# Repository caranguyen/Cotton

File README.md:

# Cotton
Contains project files for USDA-ARS research projects

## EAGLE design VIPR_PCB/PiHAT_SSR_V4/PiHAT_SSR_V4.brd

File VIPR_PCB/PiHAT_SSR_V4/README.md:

# 4th rev of the VIPR Raspberry Pi solid state relay board
- Removed two solid-state relays to allow for high side switching and flyback diodes on solenoids
- Needing to reorient components on board to allow for better isolation of 12V solenoid power and ground from Raspberry Pi

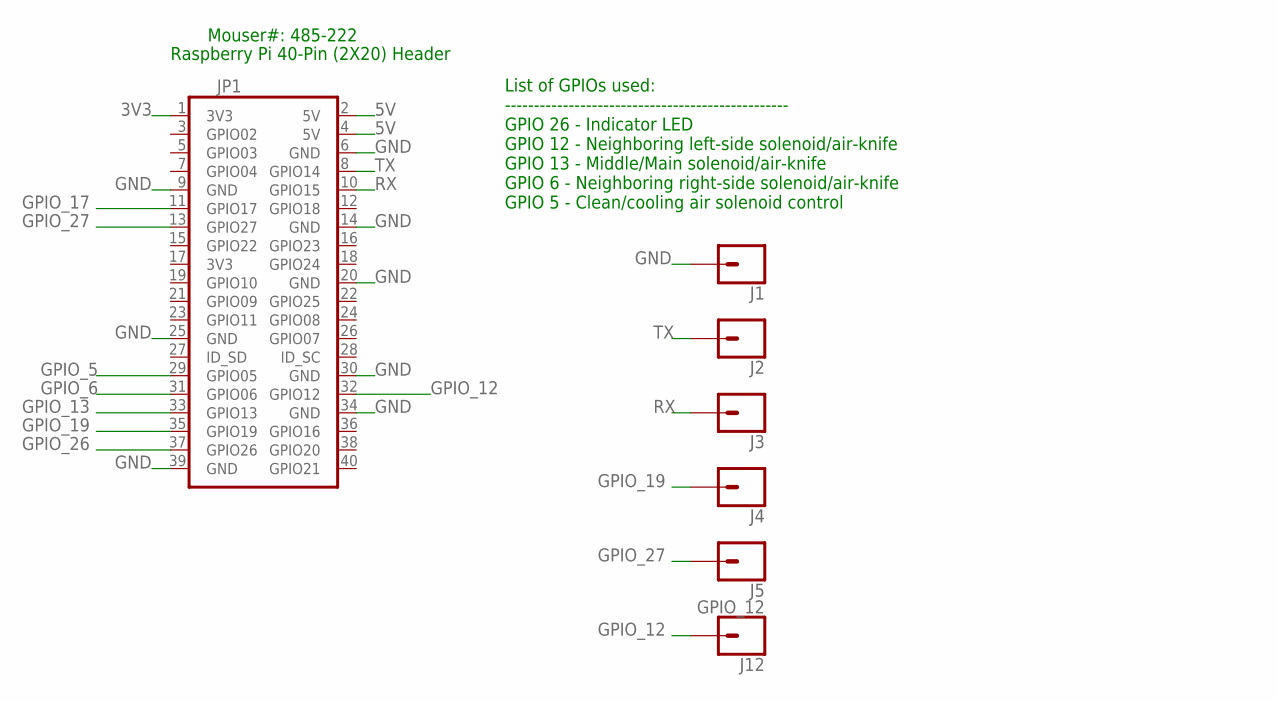
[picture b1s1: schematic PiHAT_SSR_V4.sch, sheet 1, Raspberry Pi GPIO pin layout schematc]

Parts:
J1, J2, J3, J4, J5: CONN_01; 1X01
J12: GPIO_12; 1X01
JP1: 40W_PI_HAT_TPH; 2X20

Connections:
3V3: JP1.1 (3V3); also elsewhere on the board
5V: JP1.2 (5V), JP1.4 (5V); also elsewhere on the board
GND: J1.1, JP1.6 (GND), JP1.9 (GND), JP1.14 (GND), JP1.20 (GND), JP1.25 (GND), JP1.30 (GND), JP1.34 (GND), JP1.39 (GND); also elsewhere on the board
GPIO_5: JP1.29 (GPIO05); also elsewhere on the board
GPIO_6: JP1.31 (GPIO06); also elsewhere on the board
GPIO_12: J12.1, JP1.32 (GPIO12)
GPIO_13: JP1.33 (GPIO13); also elsewhere on the board
GPIO_17: JP1.11 (GPIO17); also elsewhere on the board
GPIO_19: J4.1, JP1.35 (GPIO19)
GPIO_26: JP1.37 (GPIO26)
GPIO_27: J5.1, JP1.13 (GPIO27)
RX: J3.1, JP1.10 (GPIO15)
TX: J2.1, JP1.8 (GPIO14)

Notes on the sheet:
Raspberry Pi 40-Pin (2X20) Header
List of GPIOs used: ------------------------------------------------- GPIO 26 - Indicator LED GPIO 12 - Neighboring left-side solenoid/air-knife GPIO 13 - Middle/Main solenoid/air-knife GPIO 6 - Neighboring right-side solenoid/air-knife GPIO 5 - Clean/cooling air solenoid control
Mouser#: 485-222

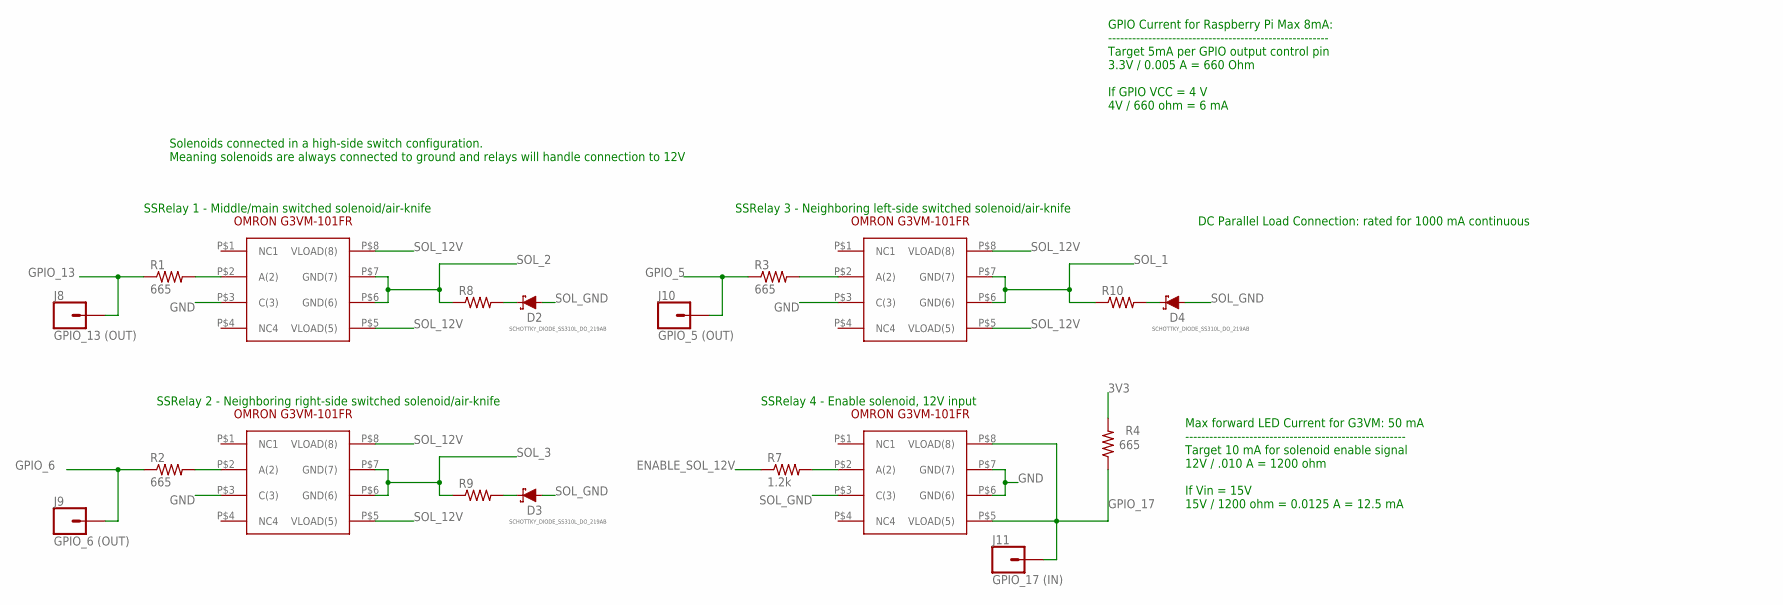
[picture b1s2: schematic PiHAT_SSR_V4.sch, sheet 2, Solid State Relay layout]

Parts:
D2, D3, D4: SCHOTTKY_DIODE_SS310L_DO_219AB; SCHOTTKY_DIODE_DO219AB
J8: GPIO_13 (OUT); 1X01
J9: GPIO_6 (OUT); 1X01
J10: GPIO_5 (OUT); 1X01
J11: GPIO_17 (IN); 1X01
R1, R2, R3, R4: 665; M0805
R7: 1.2k; M0805
R8, R9, R10: R-US_R2512; R2512
SSR1, SSR2, SSR3, SSR4: OMRON_G3VM_101FR; OMRON_G3VM-101FR

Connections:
3V3: R4.2; also elsewhere on the board
ENABLE_SOL_12V: R7.1; also elsewhere on the board
GND: SSR1.P$3 (C(3)), SSR2.P$3 (C(3)), SSR3.P$3 (C(3)), SSR4.P$6 (GND(6)), SSR4.P$7 (GND(7)); also elsewhere on the board
GPIO_5: J10.1, R3.1; also elsewhere on the board
GPIO_6: J9.1, R2.1; also elsewhere on the board
GPIO_13: J8.1, R1.1; also elsewhere on the board
GPIO_17: J11.1, R4.1, SSR4.P$5 (VLOAD(5)), SSR4.P$8 (VLOAD(8)); also elsewhere on the board
unnamed: D2.P$2 (C), R8.2
unnamed: R3.2, SSR3.P$2 (A(2))
unnamed: D3.P$2 (C), R9.2
unnamed: R2.2, SSR2.P$2 (A(2))
unnamed: R1.2, SSR1.P$2 (A(2))
unnamed: R7.2, SSR4.P$2 (A(2))
unnamed: D4.P$2 (C), R10.2
SOL_1: R10.1, SSR3.P$6 (GND(6)), SSR3.P$7 (GND(7)); also elsewhere on the board
SOL_2: R8.1, SSR1.P$6 (GND(6)), SSR1.P$7 (GND(7)); also elsewhere on the board
SOL_3: R9.1, SSR2.P$6 (GND(6)), SSR2.P$7 (GND(7)); also elsewhere on the board
SOL_12V: SSR1.P$5 (VLOAD(5)), SSR1.P$8 (VLOAD(8)), SSR2.P$5 (VLOAD(5)), SSR2.P$8 (VLOAD(8)), SSR3.P$5 (VLOAD(5)), SSR3.P$8 (VLOAD(8)); also elsewhere on the board
SOL_GND: D2.P$1 (A), D3.P$1 (A), D4.P$1 (A), SSR4.P$3 (C(3)); also elsewhere on the board

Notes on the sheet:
SSRelay 2 - Neighboring right-side switched solenoid/air-knife
SSRelay 1 - Middle/main switched solenoid/air-knife
SSRelay 3 - Neighboring left-side switched solenoid/air-knife
SSRelay 4 - Enable solenoid, 12V input
GPIO Current for Raspberry Pi Max 8mA: ------------------------------------------------------- Target 5mA per GPIO output control pin 3.3V / 0.005 A = 660 Ohm If GPIO VCC = 4 V 4V / 660 ohm = 6 mA
Max forward LED Current for G3VM: 50 mA ------------------------------------------------------- Target 10 mA for solenoid enable signal 12V / .010 A = 1200 ohm If Vin = 15V 15V / 1200 ohm = 0.0125 A = 12.5 mA
DC Parallel Load Connection: rated for 1000 mA continuous
Solenoids connected in a high-side switch configuration. Meaning solenoids are always connected to ground and relays will handle connection to 12V

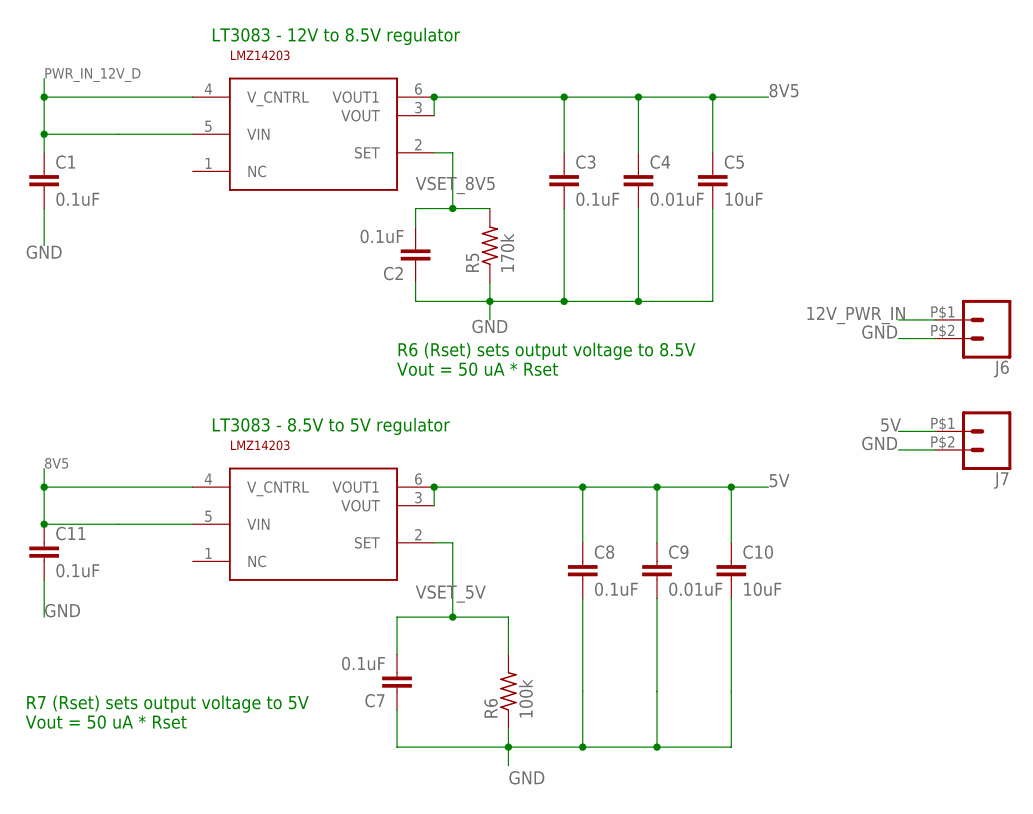
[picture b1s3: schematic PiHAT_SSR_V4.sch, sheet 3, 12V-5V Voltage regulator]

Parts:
C1, C2, C3, C7, C8, C11: 0.1uF; C0805
C4, C9: 0.01uF; C0805
C5, C10: 10uF; C0805
J6, J7: CONN_02PTH2; 1X02_BIG
R5: 170k; M0805
R6: 100k; M0805
VR1, VR2: SMD-SPECIAL_28PIN_PIC32_11_3_2011_LT3083; SMD-SPECIAL_28PIN_PIC32_11_3_2011_DPAK-5

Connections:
5V: C8.1, C9.1, C10.1, J7.P$1 (1), VR2.3 (VOUT), VR2.6 (VOUT1); also elsewhere on the board
8V5: C3.1, C4.1, C5.1, C11.1, VR1.3 (VOUT), VR1.6 (VOUT1), VR2.4 (V_CNTRL), VR2.5 (VIN)
12V_PWR_IN: J6.P$1 (1); also elsewhere on the board
GND: C1.2, C2.1, C3.2, C4.2, C5.2, C7.1, C8.2, C9.2, C10.2, C11.2, J6.P$2 (2), J7.P$2 (2), R5.1, R6.1; also elsewhere on the board
PWR_IN_12V_D: C1.1, VR1.4 (V_CNTRL), VR1.5 (VIN); also elsewhere on the board
VSET_5V: C7.2, R6.2, VR2.2 (SET)
VSET_8V5: C2.2, R5.2, VR1.2 (SET)

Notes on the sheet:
LT3083 - 12V to 8.5V regulator
R6 (Rset) sets output voltage to 8.5V Vout = 50 uA * Rset
LT3083 - 8.5V to 5V regulator
R7 (Rset) sets output voltage to 5V Vout = 50 uA * Rset

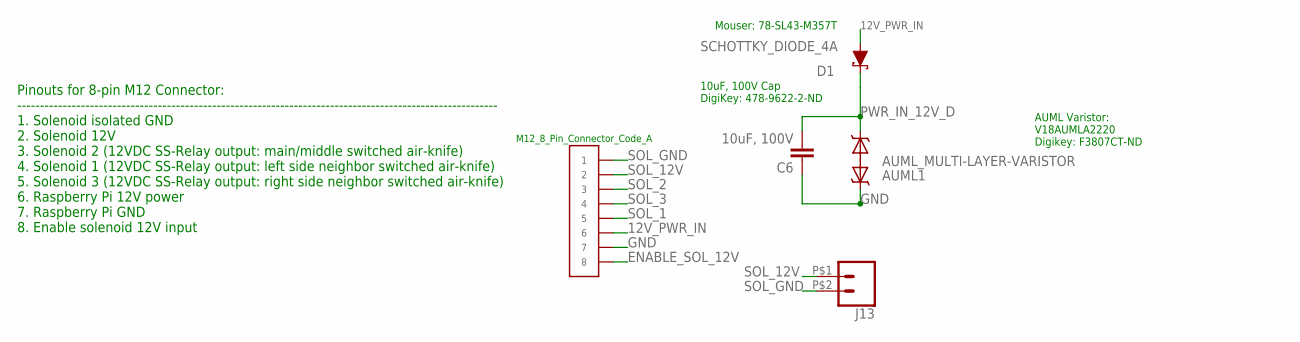
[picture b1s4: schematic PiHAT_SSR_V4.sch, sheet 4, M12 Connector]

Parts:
AUML1: SMD-SPECIAL_28PIN_PIC32_11_3_2011_MOD5_20_13_AUML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; SMD-SPECIAL_28PIN_PIC32_11_3_2011_MOD5_20_13_SMT_CAP_2220
C6: 10uF, 100V; C2220K
CN1: M12_8PIN_CODE_A
D1: SCHOTTKY_DIODE_4A; SCHOTTKY_DIODE_SMD_DO-214AB
J13: CONN_02PTH2; 1X02_BIG

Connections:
12V_PWR_IN: CN1.P$6, D1.P$2 (A); also elsewhere on the board
ENABLE_SOL_12V: CN1.P$8; also elsewhere on the board
GND: AUML1.1, C6.1, CN1.P$7; also elsewhere on the board
PWR_IN_12V_D: AUML1.2, C6.2, D1.P$1 (C); also elsewhere on the board
SOL_1: CN1.P$5; also elsewhere on the board
SOL_2: CN1.P$3; also elsewhere on the board
SOL_3: CN1.P$4; also elsewhere on the board
SOL_12V: CN1.P$2, J13.P$1 (1); also elsewhere on the board
SOL_GND: CN1.P$1, J13.P$2 (2); also elsewhere on the board

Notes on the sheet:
Pinouts for 8-pin M12 Connector: ---------------------------------------------------------------------------------------------------------- 1. Solenoid isolated GND 2. Solenoid 12V 3. Solenoid 2 (12VDC SS-Relay output: main/middle switched air-knife) 4. Solenoid 1 (12VDC SS-Relay output: left side 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
AUML_MULTI-LAYER-VARISTOR
10uF, 100V Cap DigiKey: 478-9622-2-ND
AUML Varistor: V18AUMLA2220 Digikey: F3807CT-ND
Mouser: 78-SL43-M357T

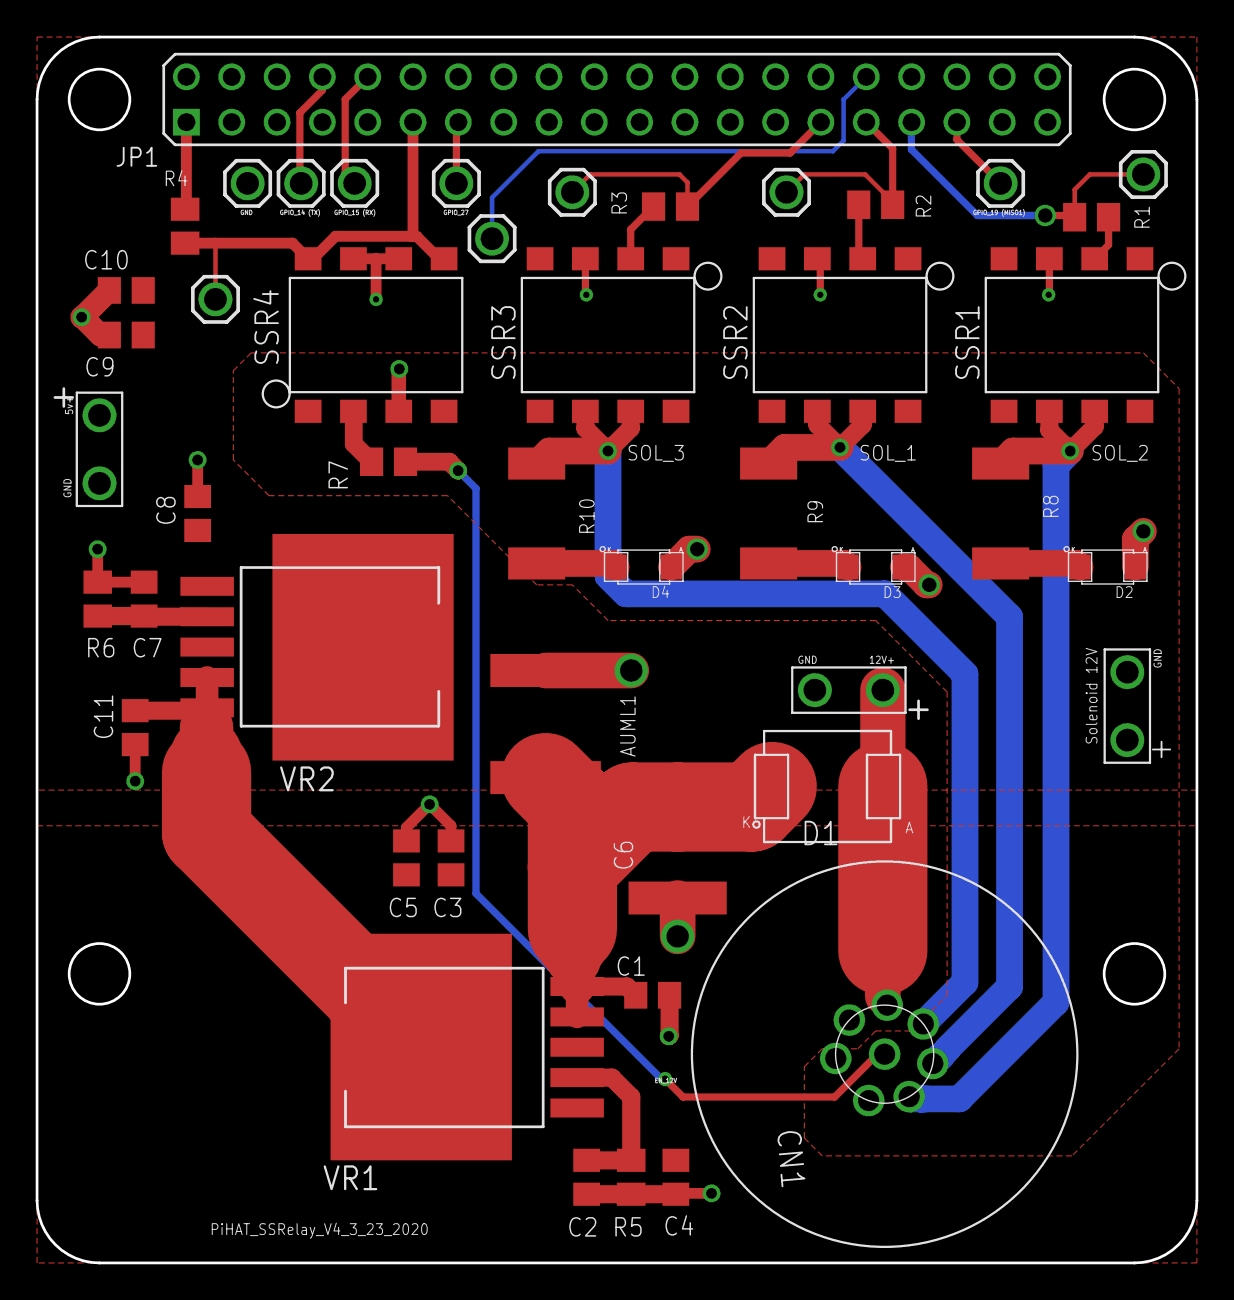
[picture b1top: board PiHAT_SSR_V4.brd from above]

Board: 2 copper layers, 65.0 x 68.7 mm, 47 parts (0 on the bottom side), 30 nets.

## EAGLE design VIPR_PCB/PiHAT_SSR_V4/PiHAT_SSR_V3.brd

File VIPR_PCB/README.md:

# VIPR PCB
Contains EAGLE files for the development of the Raspberry Pi solid-state relay board

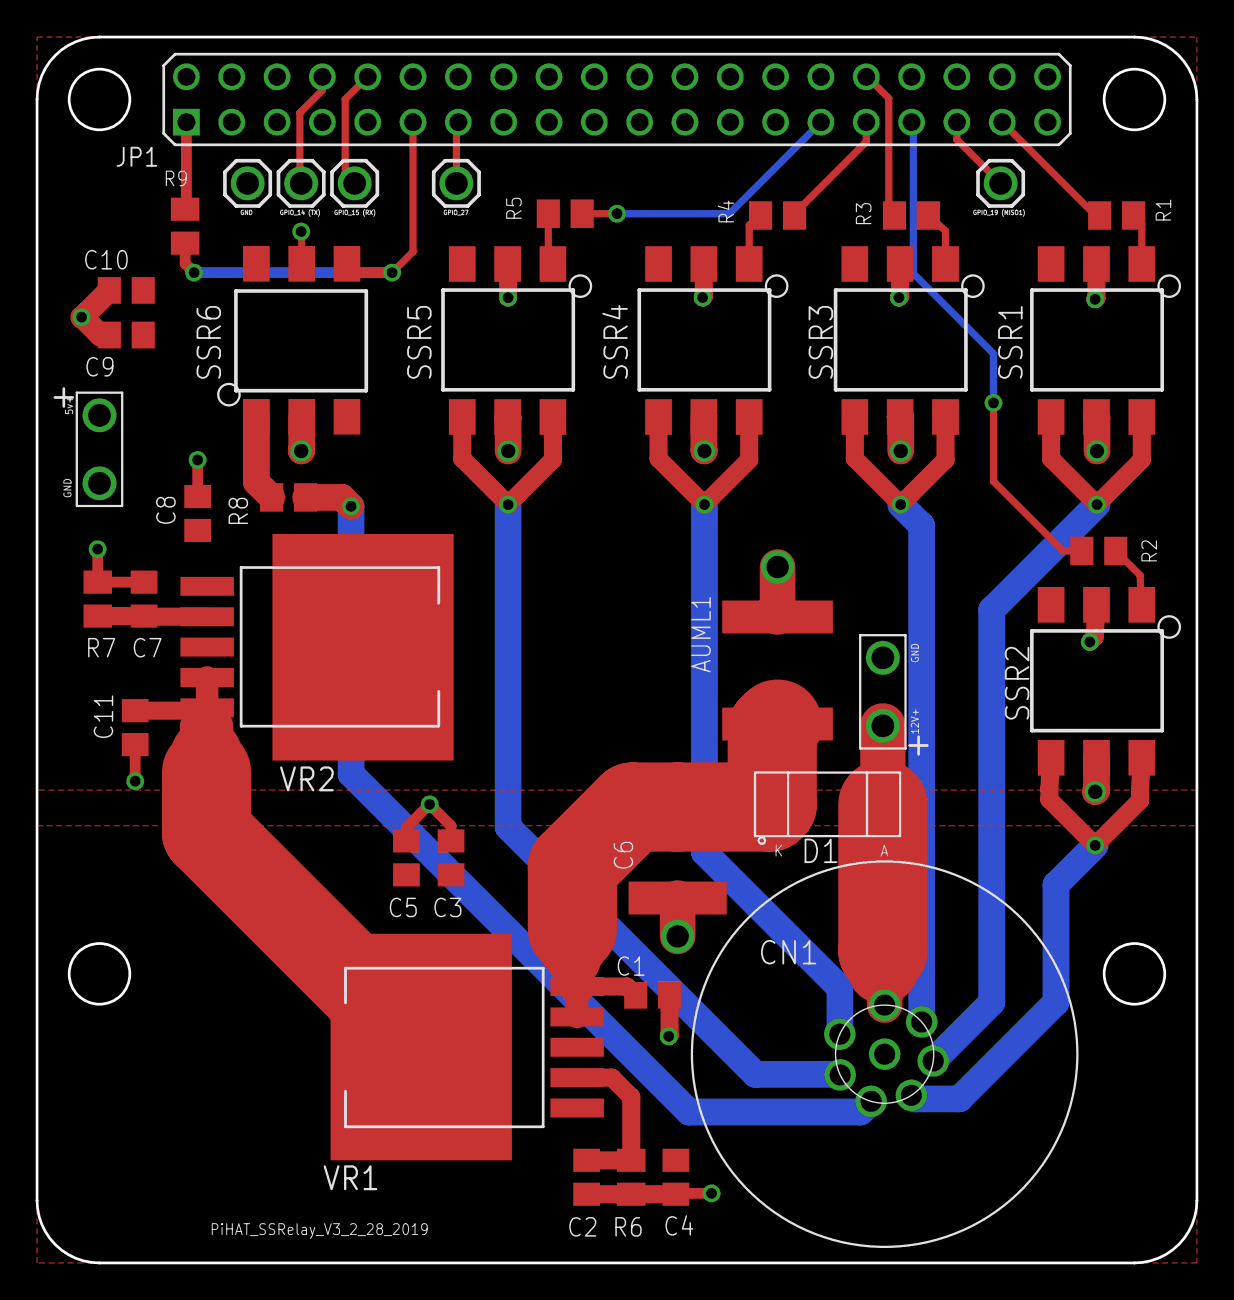
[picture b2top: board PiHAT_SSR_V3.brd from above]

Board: 2 copper layers, 65.0 x 68.7 mm, 39 parts (0 on the bottom side), 30 nets.

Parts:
AUML1: SMD-SPECIAL_28PIN_PIC32_11_3_2011_MOD5_20_13_AUML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; SMD-SPECIAL_28PIN_PIC32_11_3_2011_MOD5_20_13_SMT_CAP_2220
C1, C2, C3, C7, C8, C11: 0.1uF; C0805
C4, C9: 0.01uF; C0805
C5, C10: 10uF; C0805
C6: 10uF, 100V; C2220K
CN1: M12_8PIN_CODE_A
D1: SCHOTTKY_DIODE_4A; SCHOTTKY_DIODE_SMD_DO-214AB
J1, J2, J3, J4, J5: 1X01
J6, J7: 1X02_BIG
JP1: 2X20
R1, R2, R3, R4, R5, R9: 665; M0805
R6: 170k; M0805
R7: 100k; M0805
R8: 1.2k; M0805
SSR1, SSR2, SSR3, SSR4, SSR5, SSR6: SPARKFUN_OPTO_SSRELAY_OMRON_G3VM-61E1; SPARKFUN_6-SMD_OMRON_SSRELAY
VR1, VR2: SMD-SPECIAL_28PIN_PIC32_11_3_2011_LT3083; SMD-SPECIAL_28PIN_PIC32_11_3_2011_DPAK-5

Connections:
3V3: JP1.1, R9.2
5V: C8.1, C9.1, C10.1, J7.P$1, JP1.2, JP1.4, VR2.3, VR2.6
8V5: C3.1, C4.1, C5.1, C11.1, VR1.3, VR1.6, VR2.4, VR2.5
12V_PWR_IN: CN1.P$1, D1.P$2, J6.P$1
ENABLE_SOL_12V: CN1.P$4, R8.1
GND: AUML1.1, C1.2, C2.1, C3.2, C4.2, C5.2, C6.1, C7.1, C8.2, C9.2, C10.2, C11.2, CN1.P$8, J1.1, J6.P$2, J7.P$2, JP1.6, JP1.9, JP1.14, JP1.20, JP1.25, JP1.30, JP1.34, JP1.39, R6.1, R7.1, SSR1.2, SSR1.5, SSR2.2, SSR2.5, SSR3.2, SSR3.5, SSR4.2, SSR4.5, SSR5.2, SSR5.5, SSR6.2, SSR6.5
GPIO_5: JP1.29, R5.1
GPIO_6: JP1.31, R4.1
GPIO_12: JP1.32, R3.1
GPIO_13: JP1.33, R2.1
GPIO_17: JP1.11, R9.1, SSR6.4
GPIO_19: J4.1, JP1.35
GPIO_26: JP1.37, R1.1
GPIO_27: J5.1, JP1.13
IND_LED: CN1.P$6, SSR1.4, SSR1.6
unnamed: R1.2, SSR1.1
unnamed: R4.2, SSR4.1
unnamed: R5.2, SSR5.1
unnamed: R3.2, SSR3.1
unnamed: R2.2, SSR2.1
unnamed: R8.2, SSR6.1
PWR_IN_12V_D: AUML1.2, C1.1, C6.2, D1.P$1, VR1.4, VR1.5
RX: J3.1, JP1.10
SOL_1: CN1.P$7, SSR3.4, SSR3.6
SOL_2: CN1.P$5, SSR2.4, SSR2.6
SOL_3: CN1.P$2, SSR4.4, SSR4.6
SOL_CLEAN_COOL: CN1.P$3, SSR5.4, SSR5.6
TX: J2.1, JP1.8
VSET_5V: C7.2, R7.2, VR2.2
VSET_8V5: C2.2, R6.2, VR1.2

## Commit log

2020-03-20 Rename README.txt to README.md
2020-03-24 Created using Colaboratory
